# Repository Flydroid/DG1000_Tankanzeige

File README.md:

DG1000_Tankanzeige
==================

Tankanzeige für die DG1000J

Es wird er Füllstand des Tankes für die Turbine angezeigt

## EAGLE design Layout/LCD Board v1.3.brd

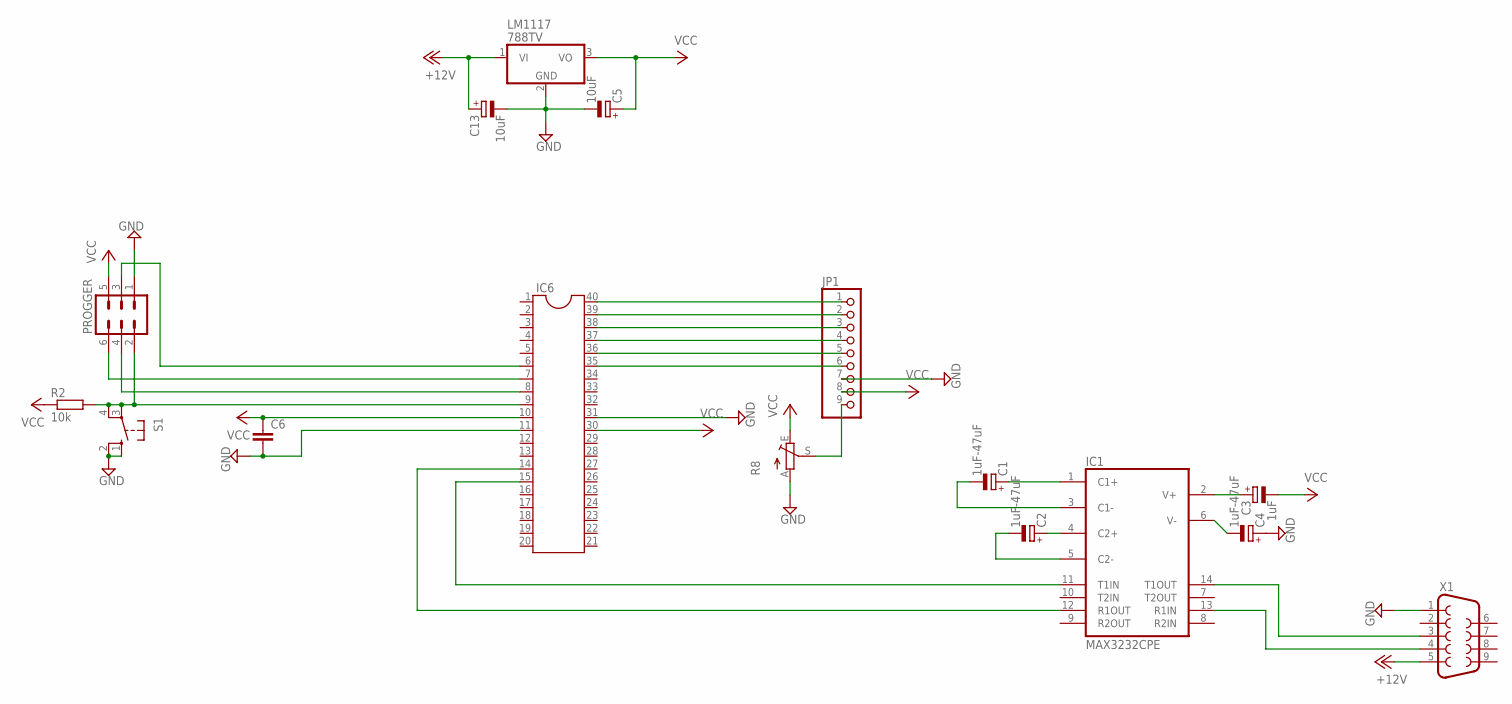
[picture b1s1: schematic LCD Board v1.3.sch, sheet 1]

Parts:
C1: 1uF-47uF; TT5D7
C2, C4: 1uF-47uF; E2,5RE
C3: 1uF; TT5D7
C5: 10uF; E3,5-8
C6: C-EU025-030X050; C025-030X050
C13: 10uF; E2,5RE
IC1: MAX3232CPE; DIL16
IC6: DIL40
JP1: PINHD-1X9; 1X09
LM1117: 788TV; TO220V
PROGGER: MA03-2
R2: 10k; 0207/7
R8: TRIM_EU-CA6V; CA6V
S1: 10-XX; B3F-10XX
X1: F09H

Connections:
$N4: C4.+, C5.-, C6.2, C13.-, IC1.15 (GND), IC6.11, IC6.31, JP1.7, LM1117.2 (GND), PROGGER.1, R8.A, S1.1 (S), S1.2 (S1), X1.1; also elsewhere on the board
+12V: C13.+, LM1117.1 (VI), X1.5; also elsewhere on the board
unnamed: IC6.7, PROGGER.6
unnamed: IC6.8, PROGGER.4
unnamed: IC6.9, PROGGER.2, R2.2, S1.3, S1.4 (P1)
unnamed: IC6.6, PROGGER.3
unnamed: C1.+, IC1.1 (C1+)
unnamed: C1.-, IC1.3 (C1-)
unnamed: C2.+, IC1.4 (C2+)
unnamed: C2.-, IC1.5 (C2-)
unnamed: C3.+, IC1.2 (V+)
unnamed: C4.-, IC1.6 (V-)
unnamed: IC1.11 (T1IN), IC6.15
unnamed: IC1.12 (R1OUT), IC6.14
unnamed: IC1.13 (R1IN), X1.4
unnamed: IC1.14 (T1OUT), X1.3
unnamed: IC6.40, JP1.1
unnamed: IC6.39, JP1.2
unnamed: IC6.38, JP1.3
unnamed: IC6.37, JP1.4
unnamed: IC6.36, JP1.5
unnamed: IC6.35, JP1.6
unnamed: JP1.9, R8.S
VCC: C3.-, C5.+, C6.1, IC1.16 (VCC), IC6.10, IC6.30, JP1.8, LM1117.3 (VO), PROGGER.5, R2.1, R8.E; also elsewhere on the board

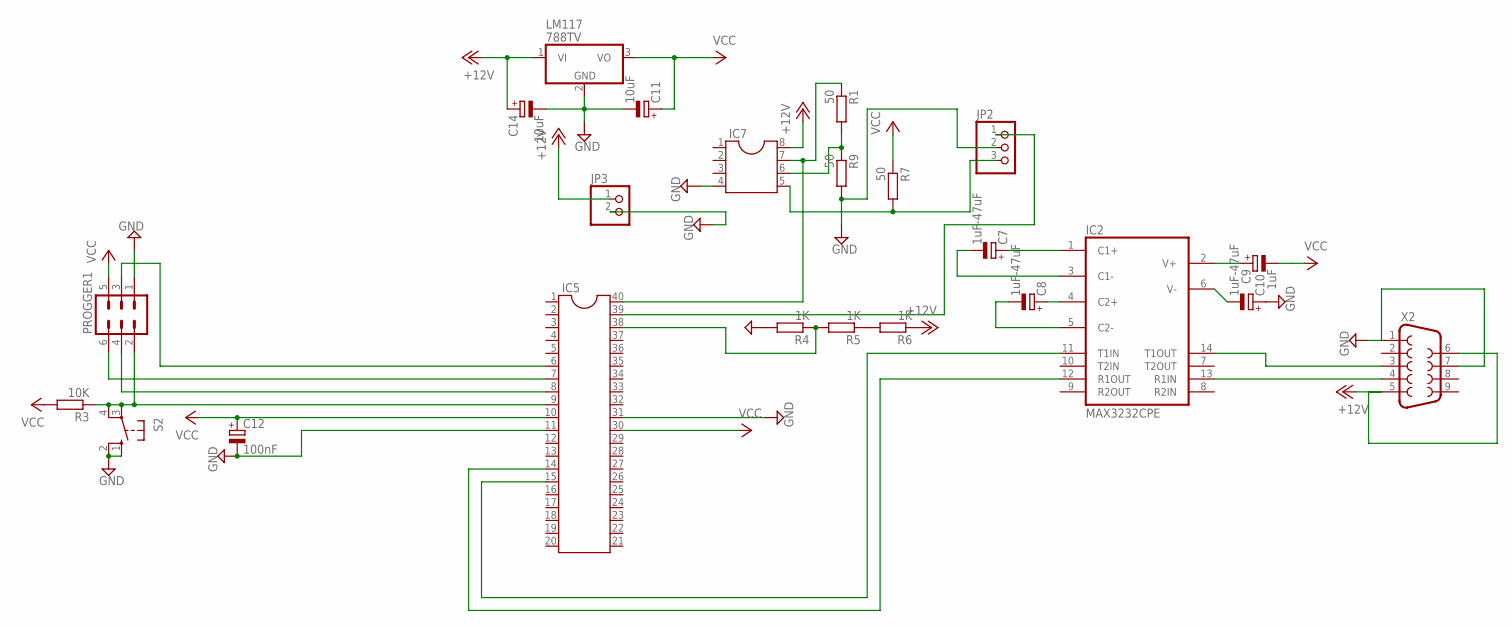
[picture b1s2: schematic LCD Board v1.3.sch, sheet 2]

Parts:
C7: 1uF-47uF; TT5D7
C8, C10: 1uF-47uF; E2,5RE
C9: 1uF; TT5D7
C11, C14: 10uF; E2,5RE
C12: 100nF; E2,5RE
IC2: MAX3232CPE; DIL16
IC5: DIL40
IC7: DIL8; DIL08
JP2: PINHD-1X3; 1X03
JP3: PINHD-1X2; 1X02
LM117: 788TV; TO220V
PROGGER1: MA03-2
R1, R9: 50; 0204/7
R3: 10K; 0207/7
R4, R5, R6: 1K; 0204/7
R7: 50; 0204/5
S2: 10-XX; B3F-10XX
X2: F09H

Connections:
$N4: C10.+, C11.-, C12.-, C14.-, IC2.15 (GND), IC5.11, IC5.31, IC7.4, JP2.2, JP3.2, LM117.2 (GND), PROGGER1.1, R4.2, R9.2, S2.1 (S), S2.2 (S1), X2.1, X2.7; also elsewhere on the board
+12V: C14.+, IC7.8, JP3.1, LM117.1 (VI), R6.1, X2.5, X2.6; also elsewhere on the board
unnamed: IC5.8, PROGGER1.4
unnamed: IC5.9, PROGGER1.2, R3.1, S2.3, S2.4 (P1)
unnamed: IC5.6, PROGGER1.3
unnamed: C7.-, IC2.3 (C1-)
unnamed: C8.+, IC2.4 (C2+)
unnamed: C8.-, IC2.5 (C2-)
unnamed: C9.+, IC2.2 (V+)
unnamed: C10.-, IC2.6 (V-)
unnamed: IC2.13 (R1IN), X2.4
unnamed: IC2.14 (T1OUT), X2.3
unnamed: IC2.11 (T1IN), IC5.15
unnamed: IC2.12 (R1OUT), IC5.14
unnamed: C7.+, IC2.1 (C1+)
unnamed: IC5.7, PROGGER1.6
unnamed: IC5.38, R4.1, R5.2
unnamed: R5.1, R6.2
unnamed: IC5.40, IC7.7, R1.1
unnamed: IC5.39, JP2.1
unnamed: IC7.5, JP2.3, R7.2
unnamed: IC7.6, R1.2, R9.1
VCC: C9.-, C11.+, C12.+, IC2.16 (VCC), IC5.10, IC5.30, LM117.3 (VO), PROGGER1.5, R3.2, R7.1; also elsewhere on the board

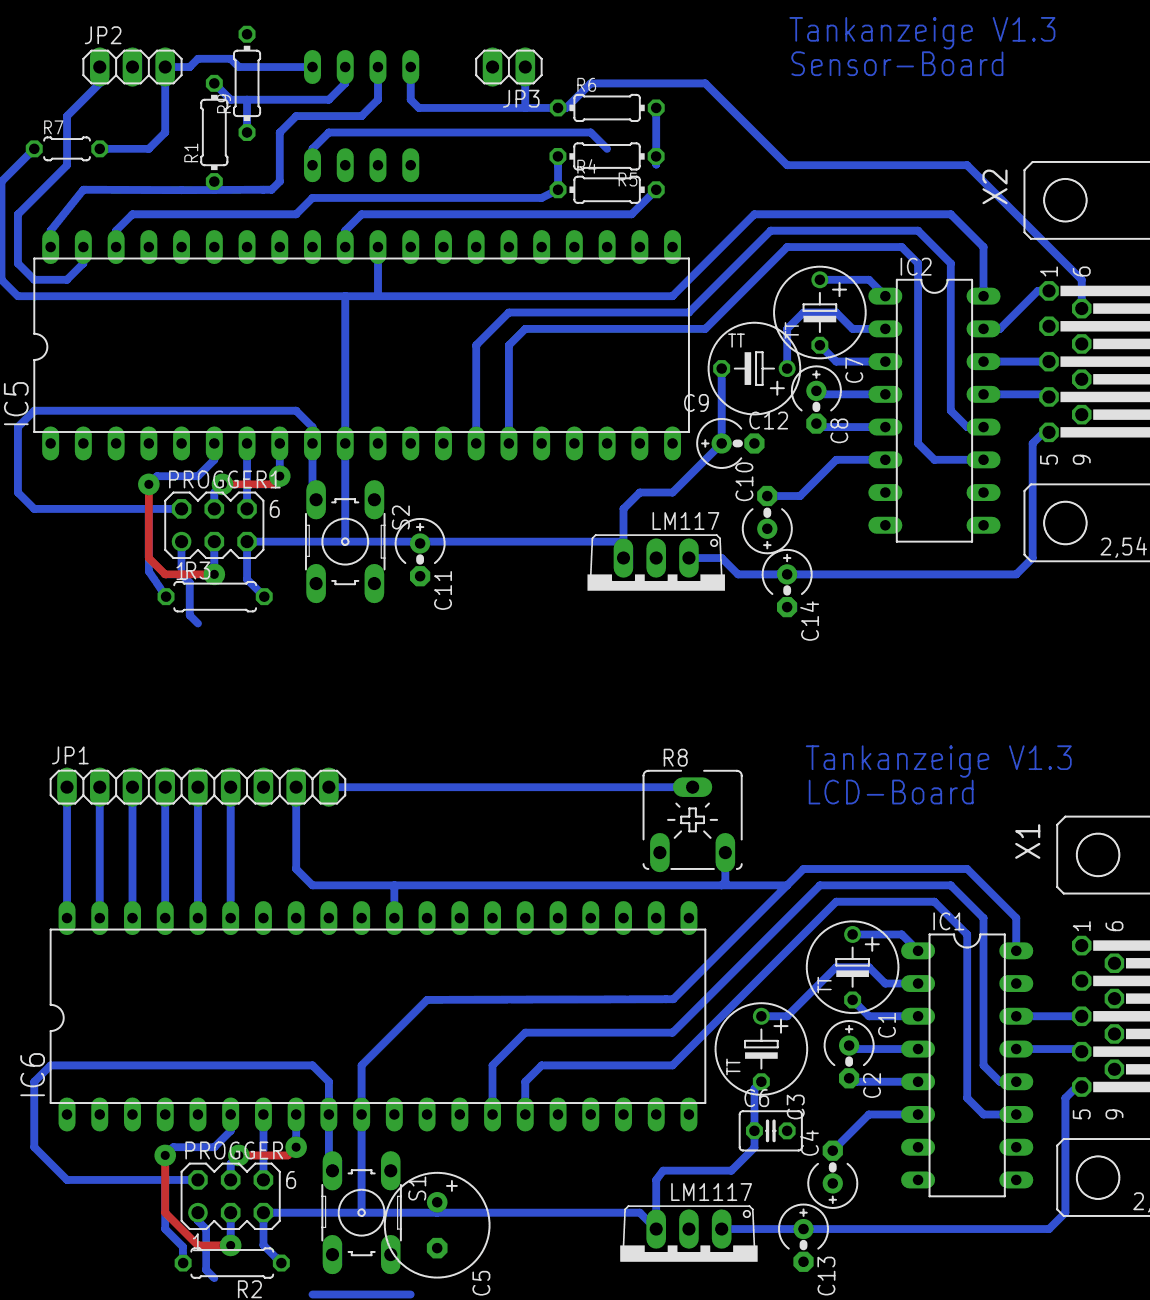
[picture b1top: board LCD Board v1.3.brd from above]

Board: 2 copper layers, 39 parts (1 on the bottom side), 44 nets.

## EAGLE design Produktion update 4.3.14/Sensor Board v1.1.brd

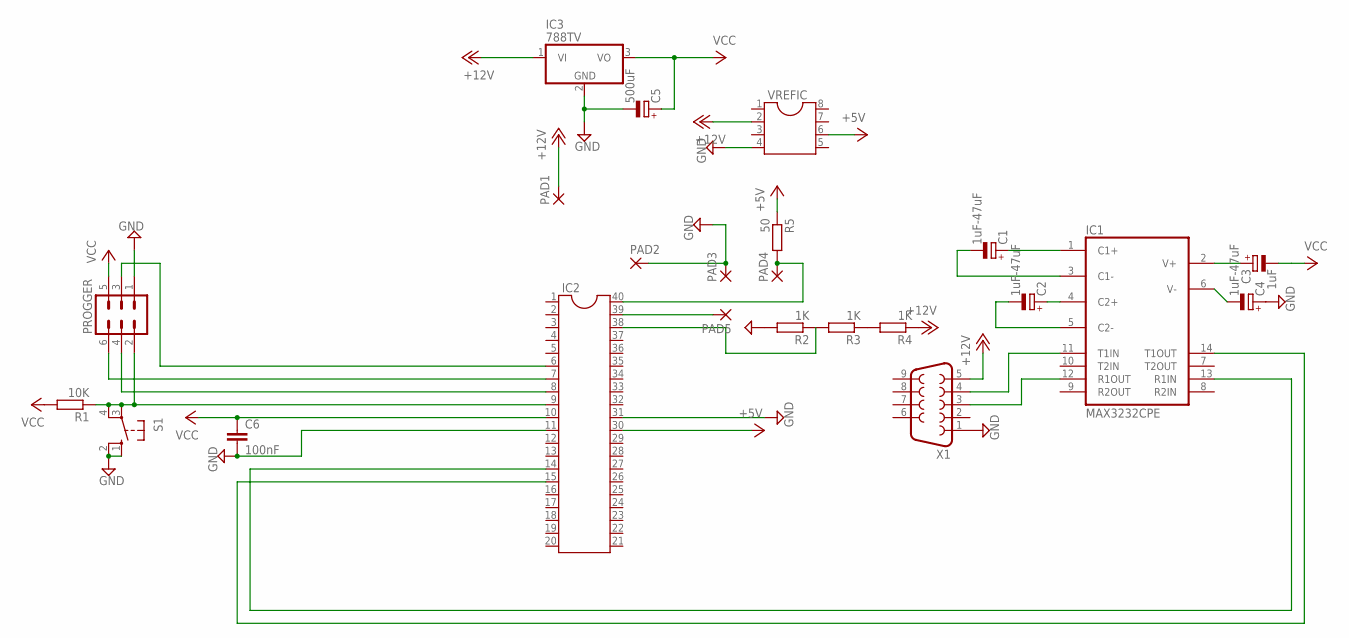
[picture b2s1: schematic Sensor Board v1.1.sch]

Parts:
C1: 1uF-47uF; TT5D7
C2, C4: 1uF-47uF; E2-4
C3: 1uF; TT5D7
C5: 500uF; E2-4
C6: 100nF; C025-030X050
IC1: MAX3232CPE; DIL16
IC2: DIL40
IC3: 788TV; TO220V
PAD1, PAD2, PAD3, PAD4, PAD5: 3,81/1,3
PROGGER: MA03-2
R1: 10K; 0204/5
R2, R3, R4: 1K; 0204/7
R5: 50; 0204/5
S1: 10-XX; B3F-10XX
VREFIC: DIL8; DIL08
X1: F09H

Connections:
+5V: IC2.30, R5.1, VREFIC.6
+12V: IC3.1 (VI), PAD1.1, R4.1, VREFIC.2, X1.5
GND: C4.+, C5.-, C6.2, IC1.15 (GND), IC2.11, IC2.31, IC3.2 (GND), PAD2.1, PAD3.1, PROGGER.1, R2.2, S1.1 (S), S1.2 (S1), VREFIC.4, X1.1
unnamed: IC2.7, PROGGER.6
unnamed: IC2.8, PROGGER.4
unnamed: IC2.9, PROGGER.2, R1.1, S1.3, S1.4 (P1)
unnamed: IC2.6, PROGGER.3
unnamed: C1.+, IC1.1 (C1+)
unnamed: C1.-, IC1.3 (C1-)
unnamed: C2.+, IC1.4 (C2+)
unnamed: C2.-, IC1.5 (C2-)
unnamed: C3.+, IC1.2 (V+)
unnamed: C4.-, IC1.6 (V-)
unnamed: IC1.14 (T1OUT), IC2.15
unnamed: IC1.13 (R1IN), IC2.14
unnamed: IC1.11 (T1IN), X1.4
unnamed: IC1.12 (R1OUT), X1.3
unnamed: IC2.40, PAD4.1, R5.2
unnamed: IC2.39, PAD5.1
unnamed: IC2.38, R2.1, R3.2
unnamed: R3.1, R4.2
VCC: C3.-, C5.+, C6.1, IC1.16 (VCC), IC2.10, IC3.3 (VO), PROGGER.5, R1.2

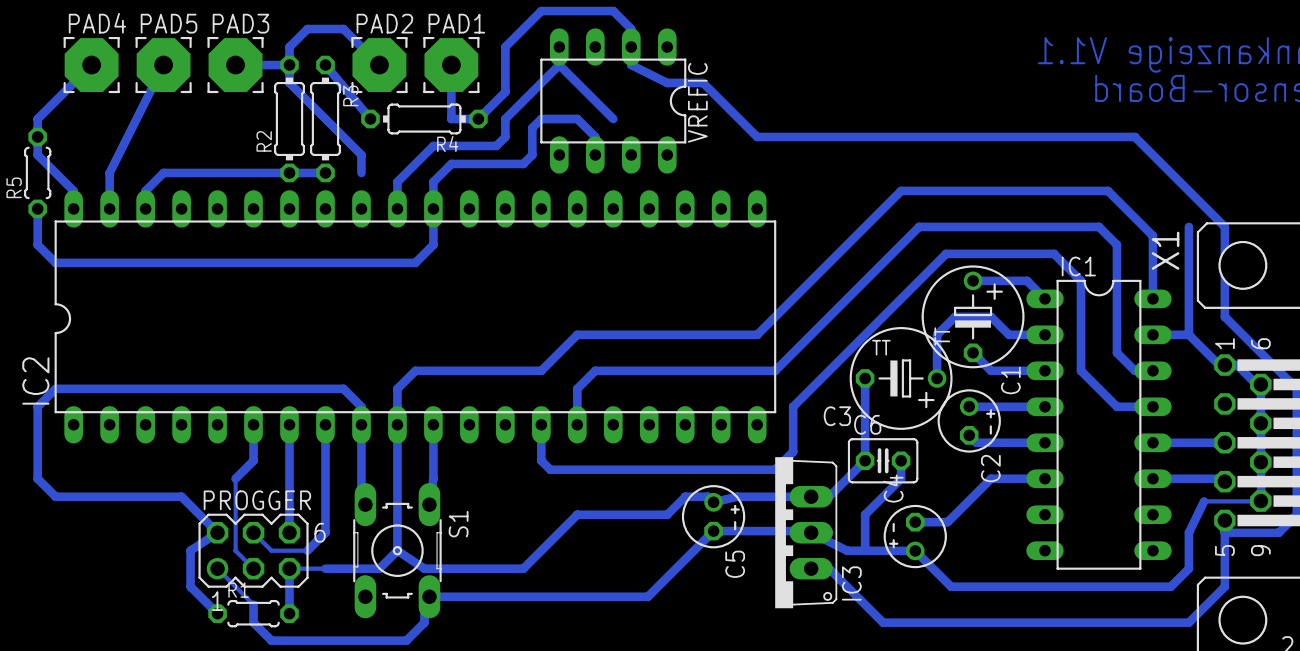
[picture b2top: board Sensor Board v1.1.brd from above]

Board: 2 copper layers, 23 parts (0 on the bottom side), 22 nets.

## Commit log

2014-03-14 Schaltplan + Layout
2014-03-14 2. Versucht
2014-03-14 3. Versuch
2014-03-14 noch einmal
2014-03-14 versions nummern update
2014-03-15 Spannungsregler zu lm1117 und Input Cap hinzugefügt
2014-03-18 Kleinere Layoutchanges und Layouts zum Ausdrucken
    Messplatine hinzugefüg
2014-03-18 ignore
